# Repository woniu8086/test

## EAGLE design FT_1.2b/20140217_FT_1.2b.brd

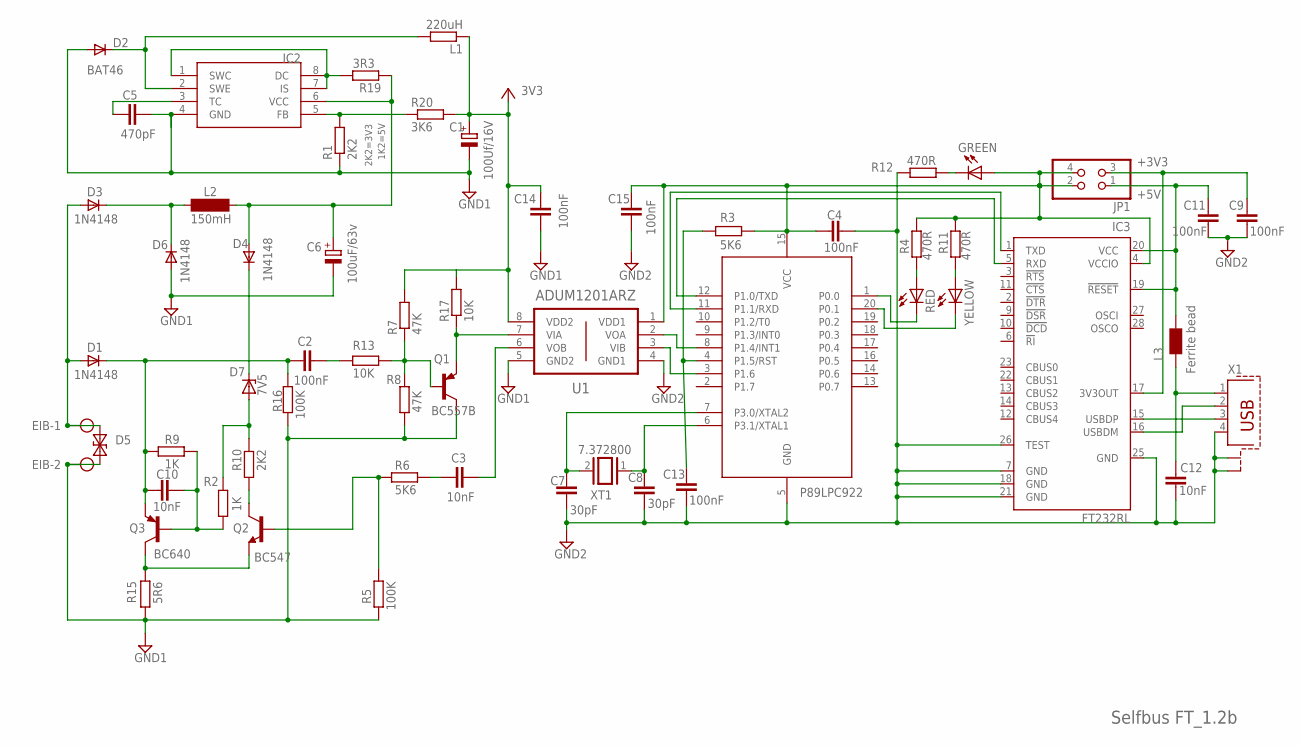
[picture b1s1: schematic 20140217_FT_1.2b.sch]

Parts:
C1: 100Uf/16V; E2,5-6
C2, C4, C9, C11, C13, C14, C15: 100nF; C0805
C3, C10, C12: 10nF; C0805
C5: 470pF; C0805
C6: 100uF/63v; E5-8,5
C7, C8: 30pF; C0805
D1, D3, D4, D6: 1N4148; SOD80_DO213AA_MINIMELF
D2: BAT46; SOD80_DO213AA_MINIMELF
D5: SMAJ43CA; SMA
D7: 7V5; SOD80C
EIB: MKDSN1,5/2-5,08
GREEN: LED3MM
IC1: 89LPC922; DIL20
IC2: MC34063AP; DIL08
IC3: FT232RL; SSOP28
JP1: PINHD-2X2; 2X02
L1: 220uH; 0207/10
L2: 150mH; SD12_1000
L3: Ferrite bead; 0805
Q1: BC557B; TO92-EBC
Q2: BC547; TO92-EBC
Q3: BC640; TO92-BCE
R1, R10: 2K2; R0805
R2, R9: 1K; R0805
R3, R6: 5K6; R0805
R4, R11, R12: 470R; R0805
R5, R16: 100K; R0805
R7, R8: 47K; R0805
R13, R17: 10K; R0805
R15: 5R6; 0204/7
R19: 3R3; R0805
R20: 3K6; R0805
RED: LED3MM
U1: ADUM1201ARZ; SOIC127P600X175-8N
X1: PN61729-S
XT1: 7.372800; QS
YELLOW: LED3MM

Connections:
DRAIN: C2.1, C10.1, D1.C, Q3.E, R9.1, R16.2
unnamed: C3.1, R6.2
unnamed: C2.2, R13.1
unnamed: IC2.5 (FB), R1.2, R20.1
unnamed: IC2.1 (SWC), IC2.7 (IS), IC2.8 (DC), R19.1
unnamed: C3.2, U1.6 (VOB)
unnamed: Q2.C, R10.1
unnamed: Q2.E, Q3.C, R15.2
unnamed: D3.C, D6.C, L2.1
unnamed: D4.C, D7.C
unnamed: Q2.B, R5.1, R6.1
unnamed: C5.1, IC2.3 (TC)
unnamed: Q1.B, R7.1, R8.2, R13.2
unnamed: D1.A, D3.A, D5.2, EIB.1
unnamed: C4.2, C15.2, GREEN.A, IC1.15 (VCC), IC3.4 (VCCIO), JP1.2, JP1.4, R3.1, R4.1, R11.1, U1.1 (VDD1)
unnamed: C8.2, IC1.6 (P3.1/XTAL1), XT1.1
unnamed: IC1.11 (P1.1/RXD), IC3.1 (TXD)
unnamed: C13.2, IC1.4 (P1.5/RST), R3.2
unnamed: IC1.12 (P1.0/TXD), IC3.5 (RXD)
unnamed: R4.2, RED.A
unnamed: R11.2, YELLOW.A
unnamed: IC1.20 (P0.1), YELLOW.K (C)
unnamed: IC1.1 (P0.0), RED.K (C)
unnamed: C11.1, IC3.19 (!RESET), IC3.20 (VCC), JP1.1, L3.2
unnamed: IC3.15 (USBDP), X1.3
unnamed: IC3.16 (USBDM), X1.2
unnamed: C9.1, IC3.17 (3V3OUT), JP1.3
unnamed: C12.1, L3.1, X1.1
unnamed: GREEN.K (C), R12.1
unnamed: C6.+, D4.A, IC2.6 (VCC), L2.2, R19.2
unnamed: IC1.8 (P1.4/INT1), U1.2 (VOA)
unnamed: R7.2, R17.2
unnamed: D2.C, IC2.2 (SWE), L1.2
unnamed: IC1.3 (P1.6), U1.3 (VIB)
unnamed: C1.-, C5.2, C6.-, C14.1, D2.A, D5.1, D6.A, EIB.2, IC2.4 (GND), Q1.C, R1.1, R5.2, R8.1, R15.1, R16.1, U1.5 (GND2)
unnamed: C4.1, C7.1, C8.1, C9.2, C11.2, C12.2, C13.1, C15.1, IC1.5 (GND), IC3.7 (GND), IC3.18 (GND), IC3.21 (GND), IC3.25 (GND), IC3.26 (TEST), R12.2, U1.4 (GND1), X1.4, X1.S1, X1.S2
unnamed: C1.+, C14.2, L1.1, R20.2, U1.8 (VDD2)
unnamed: C10.2, Q3.B, R2.2, R9.2
unnamed: Q1.E, R17.1, U1.7 (VIA)
unnamed: C7.2, IC1.7 (P3.0/XTAL2), XT1.2
REF: D7.A, R2.1, R10.2

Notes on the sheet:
P89LPC922
+5V
+3V3
2K2=3V3
1K2=5V
Selfbus FT_1.2b

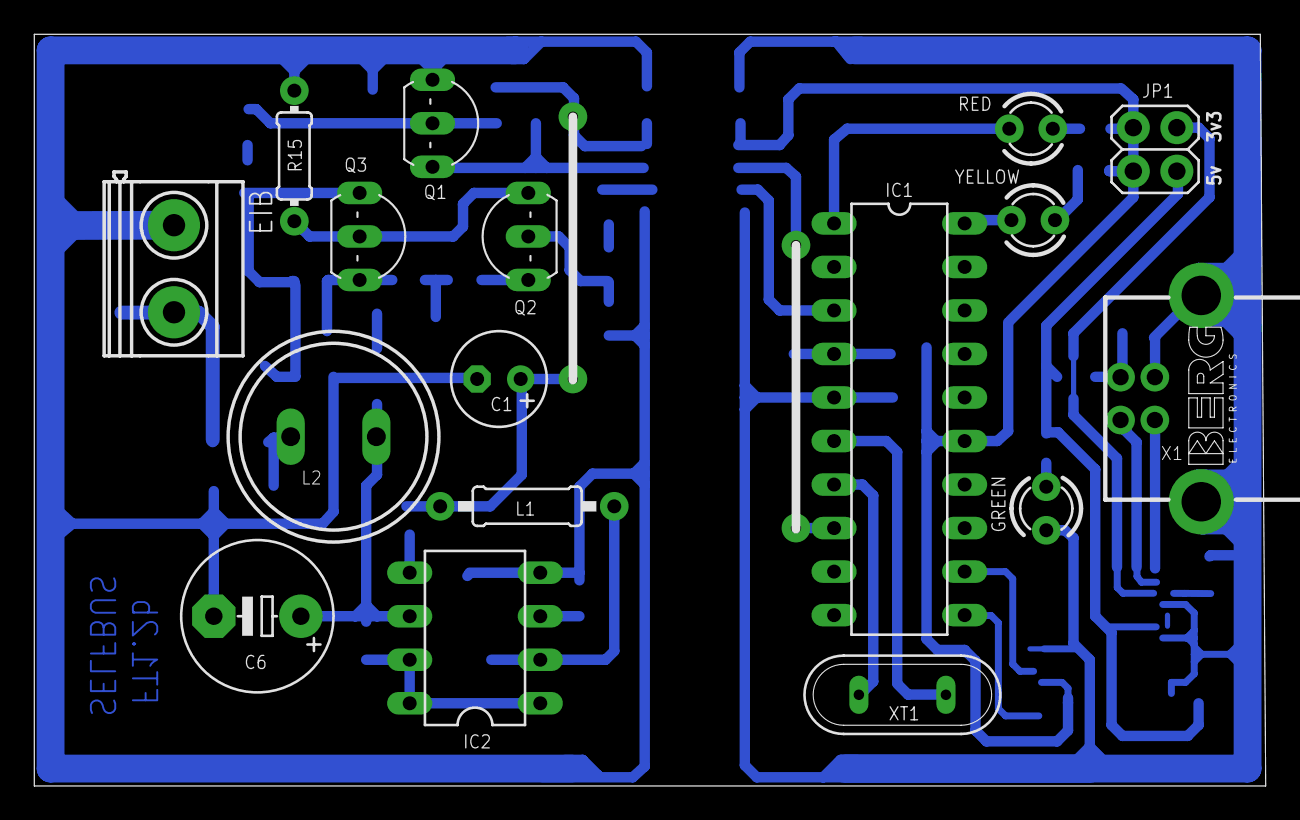
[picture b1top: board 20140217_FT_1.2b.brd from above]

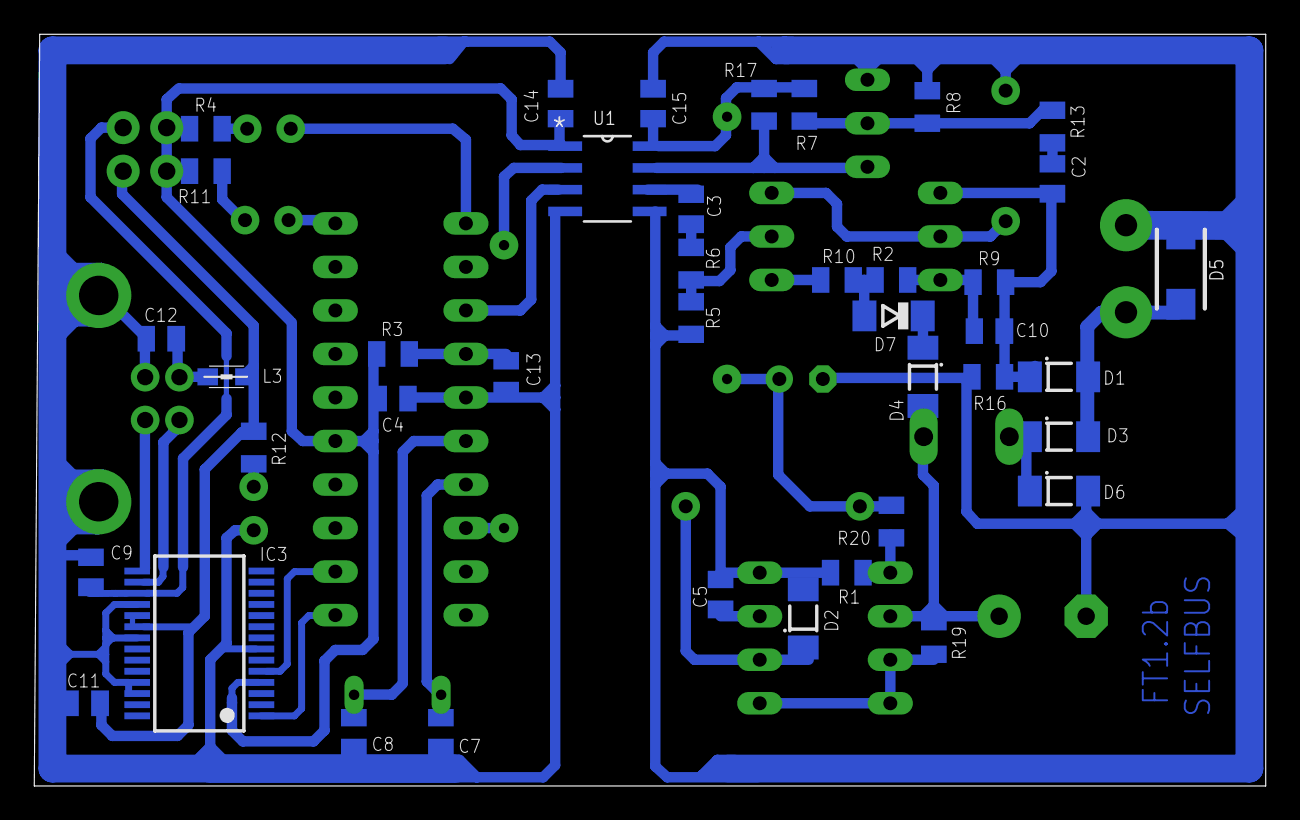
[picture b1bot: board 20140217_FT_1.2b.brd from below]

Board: 2 copper layers, 71.9 x 43.9 mm, 57 parts (40 on the bottom side), 41 nets.

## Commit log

2014-03-15 test 00
2014-03-15 testing version
2014-03-15 change directories
2014-03-17 ft12b 17/3/2014

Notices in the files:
parts and their libraries:
wuerth-elektronik: Copyright: Würth Elektronik eiSos
